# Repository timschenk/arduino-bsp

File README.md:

BSP Eurorack Breakout
=====================

Eurorack breakout box for Beatstep Pro. It takes one midi in and has 14 CV outs (8+3+3). This is the first use case.
As it takes MIDI in you can use it with any midi device.

Thoughts
========

You can see this as a general development board, to test ideas.
It uses 6 analog channels and 9 digital channels (4 pwm channels).
All channels can be set as input or output by software.

As far as I understood, its possible to set 2 pwm channels to 16 bit by software (http://playground.arduino.cc/Code/Timer1).
You could have a higher bit depth (default is 10 Bit) on analog inputs with oversampling.

There is still enough free memory on the arduino to hold code. There could be with MIDI CC selectable functions.
One could be a humanize function to delay messages for a random time or to randomize velocity.
An other could be a chord function, whenever there comes a note on SEQ1/SEQ2 in, it sends a chord for this note. And so on...

Requirements:
=============

https://github.com/wizard97/ArduinoRingBuffer

https://github.com/FortySevenEffects/arduino_midi_library.git

this is just a sketch / work in progress by http://tim-schenk.de

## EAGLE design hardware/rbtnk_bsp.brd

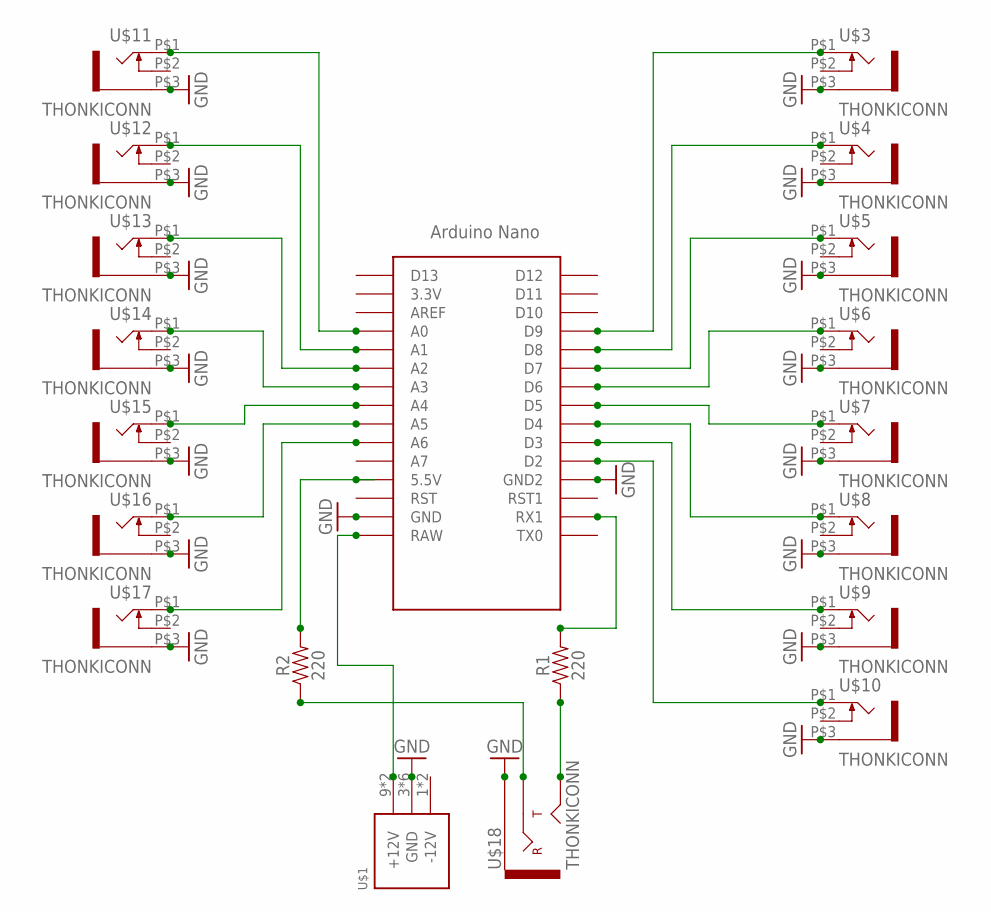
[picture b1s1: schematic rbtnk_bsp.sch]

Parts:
R1, R2: 220; 0603
U$1: POWER_SIMPLE10; POWER_10
U$2: NANO
U$3, U$4, U$5, U$6, U$7, U$8, U$9, U$10, U$11, U$12, U$13, U$14, U$15, U$16, U$17, U$18: THONKICONN

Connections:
GND: U$1.3 (GND), U$1.4 (GND), U$1.5 (GND), U$1.6 (GND), U$1.7 (GND), U$1.8 (GND), U$2.GND, U$2.GND1 (GND2), U$3.P$3 (1), U$4.P$3 (1), U$5.P$3 (1), U$6.P$3 (1), U$7.P$3 (1), U$8.P$3 (1), U$9.P$3 (1), U$10.P$3 (1), U$11.P$3 (1), U$12.P$3 (1), U$13.P$3 (1), U$14.P$3 (1), U$15.P$3 (1), U$16.P$3 (1), U$17.P$3 (1), U$18.P$1 (EARTH)
unnamed: U$2.A0, U$11.P$1 (2)
unnamed: U$2.A1, U$12.P$1 (2)
unnamed: U$2.A2, U$13.P$1 (2)
unnamed: U$2.A3, U$14.P$1 (2)
unnamed: U$2.A4, U$15.P$1 (2)
unnamed: U$2.A5, U$16.P$1 (2)
unnamed: U$2.A6, U$17.P$1 (2)
unnamed: U$2.D2, U$10.P$1 (2)
unnamed: U$2.D3, U$9.P$1 (2)
unnamed: U$2.D4, U$8.P$1 (2)
unnamed: U$2.D5, U$7.P$1 (2)
unnamed: U$2.D6, U$6.P$1 (2)
unnamed: U$2.D7, U$5.P$1 (2)
unnamed: U$2.D8, U$4.P$1 (2)
unnamed: U$2.D9, U$3.P$1 (2)
unnamed: R2.2, U$2.5V (5.5V)
unnamed: R2.1, U$18.P$2 (RING)
unnamed: R1.1, U$18.P$3 (TIP)
unnamed: R1.2, U$2.RX1
unnamed: U$1.9 (+12V), U$1.10 (+12V), U$2.RAW

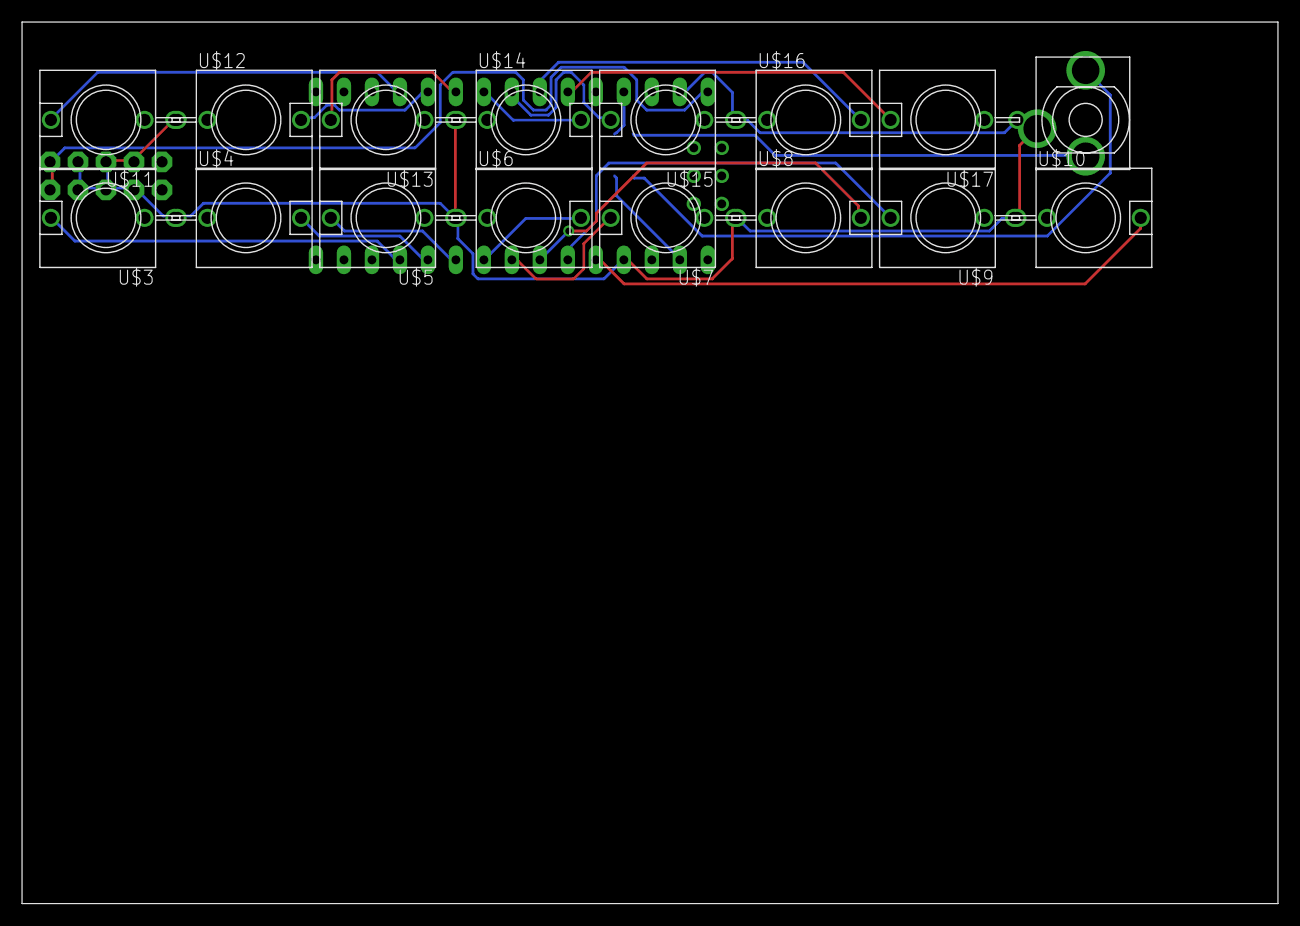
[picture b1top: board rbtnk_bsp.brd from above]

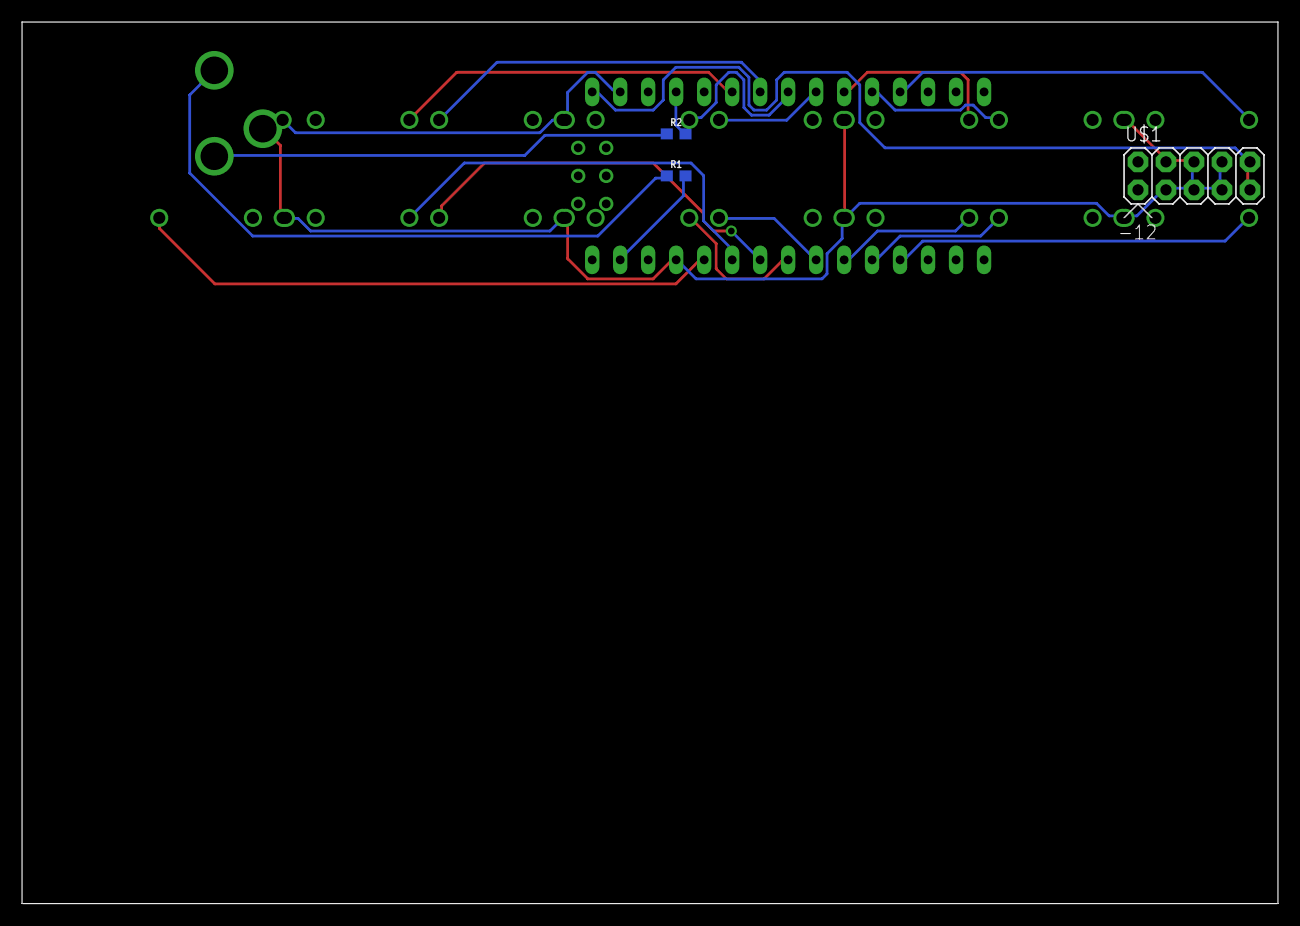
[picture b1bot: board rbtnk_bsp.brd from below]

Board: 2 copper layers, 114.0 x 80.0 mm, 20 parts (4 on the bottom side), 21 nets.

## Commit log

2017-09-30 adds readme
2017-09-30 adds basic arduino scetch
2017-09-30 readme
2017-09-30 adds basic fritzing sketch
2017-09-30 adds basic fritzing sketch png
2017-09-30 edits readme
2017-09-30 adds libraries, circuit layout v0.0.2
2017-10-01 changes readme
2017-10-31 adds eagle layouts
2017-10-31 edits eagle layouts

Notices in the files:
parts and their libraries:
SparkFun-Resistors: Licensing: Creative Commons ShareAlike 4.0 International - https://creativecommons.org/licenses/by-sa/4.0
